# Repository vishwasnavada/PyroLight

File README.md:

# PyroLight
Automated switch bot for switches using Kemet SS-430 Sensor 

Project Link:
[PyroLight](https://www.hackster.io/vishwasnavada/pyrolight-1d4a31)

##  Initial Protype image

## Final PCB Version
### Frontside 

### Backside 

### 3D View

Here's the video Link:

I referred schematics from olimex for the esp 32 charging circuit.

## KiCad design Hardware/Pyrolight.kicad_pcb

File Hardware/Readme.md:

# Instruction
This folder contains the schematics for the add on board which directly sits on the esp32 Camera board
to program and use it as a normal PyroLight device

## 3D View

### Frontside 

### Backside

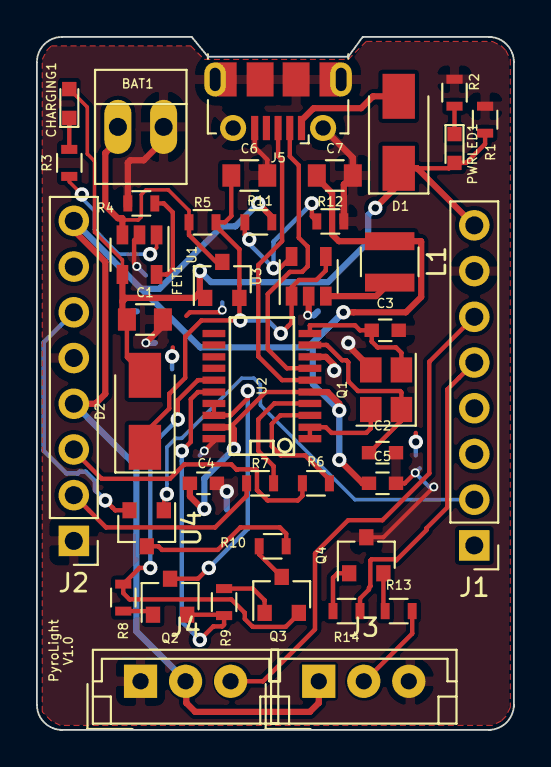
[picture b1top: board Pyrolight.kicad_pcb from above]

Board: 2 copper layers, 26.5 x 38.5 mm, 41 parts (0 on the bottom side), 33 nets.

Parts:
BAT1: DW02S; PINHEAD1-2
C1: 47uF/6.3V/; C_0805
C2: 27pF/50V/; C_0603
C3: 27pF/50V; C_0603
C4: 22uF/6.3V/; C_0603
C5: 100nF/50V/; C_0603
C6, C7: 47uF/6.3V/20%/X5R/C0805; C_0805
CHARGING1: LED/YELLOW/0603; LED_0603
D1, D2: 1N5822/SS34/SMA; D_SMA
FET1: WPM2015-3/TR; SOT-23
J1, J2: Conn_01x08_Female; Socket_Strip_Straight_1x08_Pitch2.54mm
J3: SS-430 Proximity sensor; JST_EH_B03B-EH-A_03x2.50mm_Straight
J4: Servo; JST_EH_B03B-EH-A_03x2.50mm_Straight
J5: USB_B_Micro; USB_Micro-B_Molex-105017-0001
L1: 2.2uH/1.5A/DCR<0.1R/CD32; L_Abracon_ASPI-3012S
PWRLED1: LED/RED/0603; LED_0603
Q1: Q12MHz/20pF/10ppm/4P/3.2x2.5mm; Crystal_SMD_3225-4pin_3.2x2.5mm
Q2, Q3: BC817-40(SOT23); SOT-23
Q4: BC547; SOT-23
R1: 10k/R0603; R_0603
R2, R3, R4: 2.2k/R0603; R_0603
R5: NA/R0603; R_0603
R6, R7, R10: 220R/R0603; R_0603
R8, R9: 1k/R0603; R_0603
R11: 4.99k/; R_0603
R12: 1.1k/; R_0603
R13: 1k; R_0603
R14: 10k; R_0603
U1: BL4054B-42TPRN(SOT23-5); SOT-23-5
U2: CH340T(SSOP20W); SSOP-20
U3: SY8089AAAC(SOT23-5); SOT-23-5
U4: BAT54C(SOT23-3); SOT-23

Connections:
+3V3: C4.1, C5.1, C7.1, J2.4, J2.8, J3.1, J4.2, L1.2, R11.2, U2.5, U2.19
+5V: C1.1, CHARGING1.2, D1.1, D2.2, FET1.1, J1.8, PWRLED1.2, R1.1, U1.4
/+5V_USB: D1.2, J5.1
GND: BAT1.2, C1.2, C2.2, C3.2, C4.2, C5.2, C6.2, C7.2, J1.7, J2.1, J2.5, J3.3, J4.1, J5.5, J5.6, Q1.3, Q4.3, R1.2, R2.2, R4.2, R12.2, U1.2, U2.8, U2.20, U3.2
GPIO1_TXD: J2.2, R7.2
GPIO3_RXD: J2.3, R6.2
GPIO_0: J2.6, U4.2
GPIO_02: J1.2, U4.1
GPIO_12: J1.6, J4.3
GPIO_13: J1.5, R14.1
unnamed: BAT1.1, FET1.3, R5.1, U1.3
unnamed: C2.1, Q1.1, U2.9
unnamed: C3.1, Q1.2, U2.10
unnamed: C6.1, D2.1, FET1.2, R5.2, U3.1, U3.4
unnamed: CHARGING1.1, R3.1
unnamed: J3.2, R13.2
unnamed: J5.2, U2.7
unnamed: J5.3, U2.6
unnamed: L1.1, U3.3
unnamed: PWRLED1.1, R2.1
unnamed: Q2.1, R8.2
unnamed: Q2.2, R9.1, U2.16
unnamed: Q3.1, R9.2
unnamed: Q3.2, R8.1, U2.15
unnamed: Q3.3, R10.1
unnamed: Q4.1, R14.2
unnamed: Q4.2, R13.1
unnamed: R3.2, U1.1
unnamed: R4.1, U1.5
unnamed: R6.1, U2.3
unnamed: R7.1, U2.4
unnamed: R10.2, U4.3
unnamed: R11.1, R12.1, U3.5

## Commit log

2020-03-01 Initial code
2020-03-03 Updated Schematics
2020-03-03 Updates schematics
2020-03-04 added Gerbers
2020-03-04 Added gerbers
2020-03-04 Gerber files
2020-03-04 Added other project files
2020-03-04 Added images
2020-03-04 Added 3d view Image
2020-03-04 Updated readme file with images
2020-03-05 Added initial Image
